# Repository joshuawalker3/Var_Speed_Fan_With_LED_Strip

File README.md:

# **Variable Speed Desk Fan with RGB LED for Use While Soldering**

## **Project Overview**
An annoyance I’ve had while soldering is that the fumes from the flux burning off tends to drift directly in my face and up my nose. To solve this issue, I made this desktop fan. The fan is actually a PC chassis fan and the LED strip is a cheap LED strip. Any strip will work as long as they have a 4 pin connection and are Common Anode.

## **Code**
### *Overview*
The code is written in C. No IDE was used, only sublime text editor (because it’s the superior text editor).

Overall, the code is pretty straightforward. After initializing structs representing a motor (the fan) and the LED strip, they are used to initialize their respective functions then the drivers for each are started as their own task so they can run in “parallel”. The drivers and related functions are contained in components so the code header can be linked when the ELF is built by the toolchain.

The fan is represented in the code as a Pulse Width Modulated (PWM) DC-motor. The struct is used to set up the PWM module and the GPIO pins for controlling motor speed. A 2-bit resolution for the PWM was chosen since I only desired to have three speeds for the fan: off, half-power, and full-power. The motor driver polls the GPIO pins and, when an input is detected, changes the motor speed accordingly.

The LED strip is controlled via signals from 3 GPIO pins, 1 for each color. The LED has two modes. The static mode where a chosen color is displayed indefinitely and the cycle mode where every color combination is cycled through sequentially. The LED driver polls two input pins. The first input pin cycles through colors sequentially and can cycle power to the LED if pressed for 1 second. The second input changes the LED mode.
### *Challenges and Lessons Learned*
The biggest challenge with the code was figuring out the toolchain and how the build system works. A good chunk of time was spent trying to figure out how to integrate the header into the main code. The solution to this was obviously to RTFM. The biggest lesson learned was the value of structs. By putting all needed variables into pretty little structs, the code became easier to read as well as to write.

## **Chassis Design and Manufacture**
### *Overview*
The chassis was designed in FreeCAD, sliced using Ankermake default slicer, and printed on an Ankermake M5. It was printed as one solid piece. The chassis is simply a plastic base connected to a slot for the fan and slots for the LED strip and PCB. It was designed to be as compact as possible while maintaining stability.

#### FreeCAD Model

### *Challenges and Lessons Learned*
The main challenge with the chassis was getting it to print properly. Since that are parts that are “floating” while the print is in process, supports were required for the fan slot and the circular vertical hole. The print failed twice for what is suspected to be the same reason. The solution was to simply to slow the speeds down across the board for the entire print. This caused the print time to inflate from around 11 hours to 30 hours.
#### Failed Print

#### Proper Print with Supports Connected

#### Final Print

## **PCB Design**
### *Overview*
The PCB was designed using KiCAD and manufactured through PCBWay. I changed PCB manufacturers out of curiousity but could find no signifigance between PCBWay and Seeed Fusion.

Since the fan and LED strip require 12 VDC and the ESP32 requires between 3.3 – 6 VDC, the circuit is split by a buck converter that transforms 12VDC to8 around 5 VDC (I used 4.5 VDC). The PWM signal is sent directly from the ESP board to the fan. The LED strip interfaces to the ESP board via PN-2222A transistors.

#### PCB Schematic

#### Circuit Prototype

#### PCB Design

I also added some components to aid in troubleshooting such as LED’s that indicate that power is being applied to the board when off, an indication the model is on, LED’s connected in parallel to each LED GPIO to show proper response, and an LED in parallel to the fan that shows the status of the fan since the LED will change brightness as the PWM signal, and therefore fan speed, changes.
### *Challenges and Lessons Learned*
This was a big step for me in PCB design since it had more components than I had ever used before. This meant that I had to be creative with routing traces. To further remove trace clutter on the PCB, I added via’s so I could have traces on both the top and bottom of the PCB.

#### PCB Comparison Before and After Soldering Components

#### PCB Mounted on Chassis

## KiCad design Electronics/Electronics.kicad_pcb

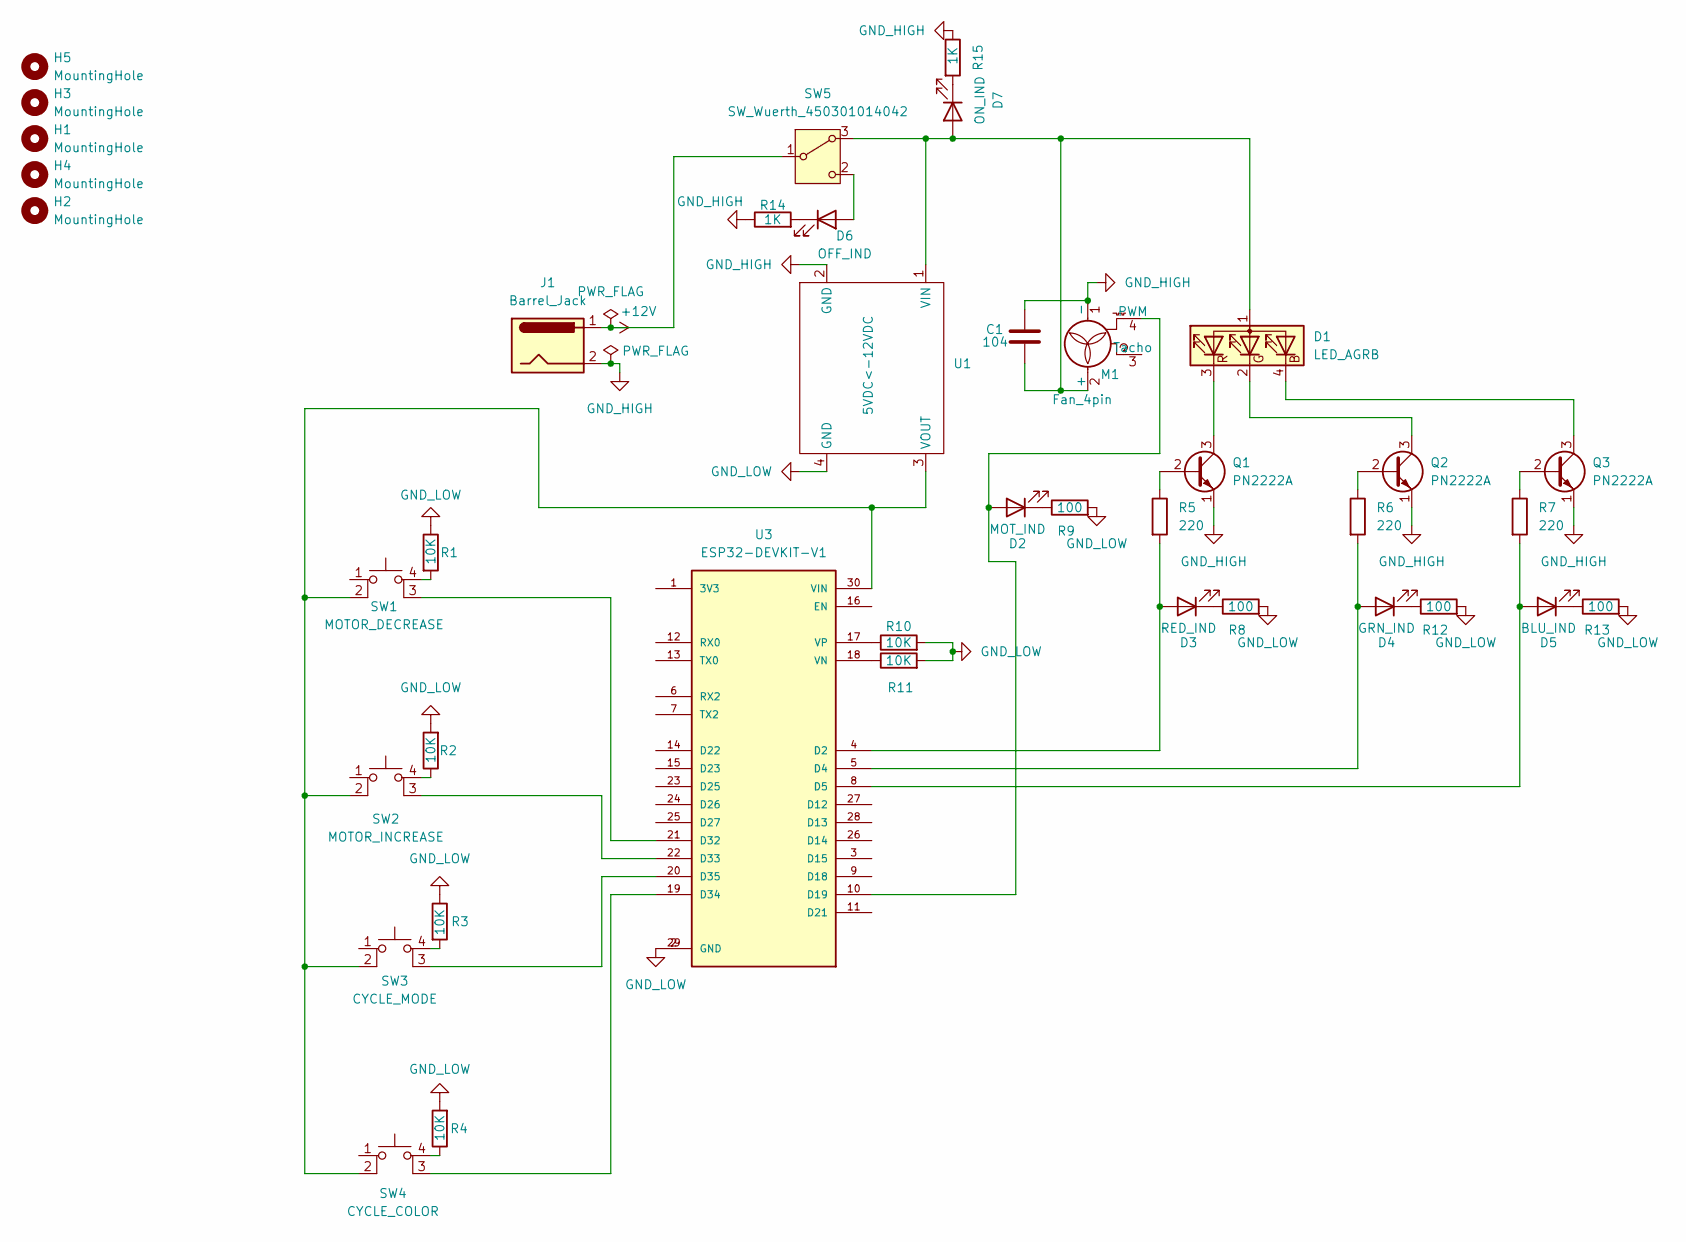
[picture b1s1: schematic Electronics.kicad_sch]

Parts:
C1: 104; C_Disc_D5.0mm_W2.5mm_P5.00mm
D1: LED_AGRB; PinHeader_1x04_P2.54mm_Vertical
D2: MOT_IND; LED_1206_3216Metric_Pad1.42x1.75mm_HandSolder
D3: RED_IND; LED_1206_3216Metric_Pad1.42x1.75mm_HandSolder
D4: GRN_IND; LED_1206_3216Metric_Pad1.42x1.75mm_HandSolder
D5: BLU_IND; LED_1206_3216Metric_Pad1.42x1.75mm_HandSolder
D6: OFF_IND; LED_1206_3216Metric_Pad1.42x1.75mm_HandSolder
D7: ON_IND; LED_1206_3216Metric_Pad1.42x1.75mm_HandSolder
H1, H2, H3, H4, H5: MountingHole; MountingHole_3.2mm_M3
J1: Barrel_Jack; BarrelJack_Wuerth_6941xx301002
M1: Fan_4pin; PinHeader_1x04_P2.54mm_Vertical
Q1, Q2, Q3: PN2222A; TO-92_Inline
R1, R2, R3, R4, R10, R11: 10K; R_1206_3216Metric_Pad1.30x1.75mm_HandSolder
R5, R6, R7: 220; R_1206_3216Metric_Pad1.30x1.75mm_HandSolder
R8, R9, R12, R13: 100; R_1206_3216Metric_Pad1.30x1.75mm_HandSolder
R14, R15: 1K; R_1206_3216Metric_Pad1.30x1.75mm_HandSolder
SW1: MOTOR_DECREASE; SW_PUSH_6mm
SW2: MOTOR_INCREASE; SW_PUSH_6mm
SW3: CYCLE_MODE; SW_PUSH_6mm
SW4: CYCLE_COLOR; SW_PUSH_6mm
SW5: SW_Wuerth_450301014042; SW_Slide-03_Wuerth-WS-SLTV_10x2.5x6.4_P2.54mm
U1: 5VDC<-12VDC; Buck_Converter
U3: ESP32-DEVKIT-V1; MODULE_ESP32_DEVKIT_V1_NO_MOUNT; PARTREV N/A

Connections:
+12V: J1.1, SW5.1 (B)
GND_HIGH: C1.1, J1.2, M1.1 (-), Q1.1 (E), Q2.1 (E), Q3.1 (E), R14.1, R15.1, U1.2 (GND)
GND_LOW: R1.1, R2.2, R3.1, R4.2, R8.2, R9.2, R10.2, R11.2, R12.2, R13.2, U1.4 (GND), U3.2 (GND), U3.29 (GND)
unnamed: C1.2, D1.1 (A), D7.2 (A), M1.2 (+), SW5.3 (A), U1.1 (VIN)
unnamed: D1.4 (BK), Q3.3 (C)
unnamed: D1.2 (GK), Q2.3 (C)
unnamed: D1.3 (RK), Q1.3 (C)
unnamed: D2.2 (A), M1.4 (PWM), U3.10 (D19)
unnamed: D2.1 (K), R9.1
unnamed: D3.2 (A), R5.2, U3.4 (D2)
unnamed: D3.1 (K), R8.1
unnamed: D4.2 (A), R6.2, U3.5 (D4)
unnamed: D4.1 (K), R12.1
unnamed: D5.2 (A), R7.2, U3.8 (D5)
unnamed: D5.1 (K), R13.1
unnamed: D6.2 (A), SW5.2 (C)
unnamed: D6.1 (K), R14.2
unnamed: D7.1 (K), R15.2
unnamed: Q1.2 (B), R5.1
unnamed: Q2.2 (B), R6.1
unnamed: Q3.2 (B), R7.1
unnamed: R1.2, SW1.4 (A)
unnamed: SW1.3 (K), U3.21 (D32)
unnamed: R2.1, SW2.4 (A)
unnamed: SW2.3 (K), U3.22 (D33)
unnamed: R3.2, SW3.4 (A)
unnamed: SW3.3 (K), U3.20 (D35)
unnamed: R4.1, SW4.4 (A)
unnamed: SW4.3 (K), U3.19 (D34)
unnamed: SW1.2, SW2.2, SW3.2, SW4.2, U1.3 (VOUT), U3.30 (VIN)
unnamed: R11.1, U3.18 (VN)
unnamed: R10.1, U3.17 (VP)

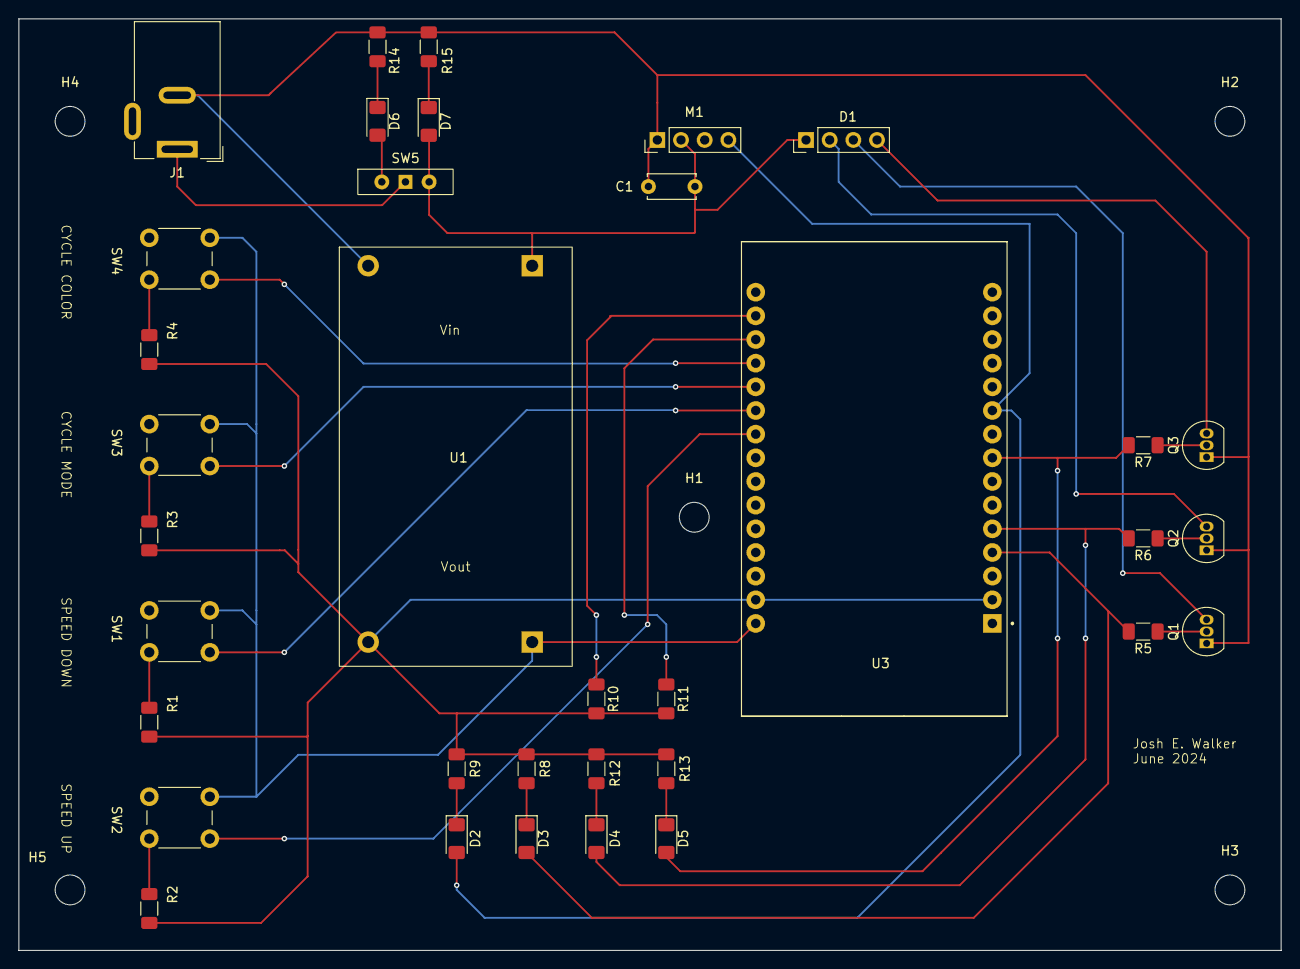
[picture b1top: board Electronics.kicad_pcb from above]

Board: 2 copper layers, 135.5 x 100.0 mm, 40 parts (0 on the bottom side), 32 nets.

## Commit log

2024-06-19 Need to finish motor component
2024-06-19 Finished. Awaiting hardware testing
2024-06-21 Added comments and formatted for readability. Awaiting testing
2024-06-21 Finished prototype. Next Step: Design Case!
2024-06-23 Added schematic
2024-06-25 Updated schematic. Working on footprints. Need to add new DevKit Symbol to schematic
2024-06-26 Began PCB design. Updated Footprints. Added Indication LEDs
2024-06-30 Finalized. Awaiting PCB Production
2024-07-08 Making progress on chassis. Need RGB Strip holder design
2024-07-08 Completed Chassis Version 1. Awaiting print
2024-07-08 Modified fan pocket. First print failed (supports issue). Reprint
2024-07-16 Final Design
2024-07-19 Finished!
2024-07-21 Added pics and README
2024-07-21 Fixed README
2024-07-21 Updated file structure
